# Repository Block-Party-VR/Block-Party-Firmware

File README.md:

# Block Party

Stack blocks in real life. See them stack in VR.
Play with blocks in VR. See them change in real life.
If you’re feeling brave, enter the doll house.

Virtual reality can be a powerful tool to connect the physical world and the digital world and connect people in different locations.
However, many VR experiences today are limited to the digital world.
Many multi-user VR experiences place all users into the same digital world and people in the VR headset are cut off from the physical world.

Block Party uses an asymmetric experience to connect a person using a VR headset with a person without a headset.
The person without a headset interacts with physical blocks on a physical board while the person in the VR headset interacts with digital blocks on a digital board.
When the physical user places a physical block on the physical board, the VR user sees a block in the corresponding location on the digital board.
When the physical user removes a block from the board, the corresponding digital block disappears for the VR user.
When the VR user hovers over or picks up a digital cube, the corresponding physical cube changes color to show the physical user what the VR user is doing.

## Setup
### Repository Setup
When the repository is first cloned you will need to initialize all of its submodules. 

In the terminal type: `git submodule update --init --recursive` which will initalize all of the submodules.

### Board Assemble
#### Parts List
- Foam core (scavenged)
- (4) Thor labs boxes (scavenged)
- (1) ESP32
- (1) breadboard
- copper tape
- (9) magnets
- (9) 10k resistors
board documentation can be found int he `documentation` directory.

### Cube Assembly
#### Parts List
- 3D printed case and cover (stl files are in the documentation folder)
- WS2812B LED (1 strip of 2 LEDs)
- (1) 10k resistor
- copper tape
- (2) magnets
- Kapton tape
- black electrical tape to mark the bottom
wiring diagram for the cube is in the `documentation` directory.

### Hardware Required
- Meta Quest headset. The included Unity project uses SDKs for Android so other Android-based headsets may work, but have not been tested.
- The physical board and physical blocks
- Two USB power sources to run the physical board. One for the LEDs and one for the sensors detecting where the blocks are.

### Software Dependencies
#### Unity
- [`the Singularity`](https://github.com/VRatMIT/TheSingularity-Unity)
- Meta Presence Platform: hand tracking, pokable item, interaction, hand-poke interaction, synthetic hands, grab interaction, hand-poke limiter, pass-through
- Unity package: [DOTween](https://assetstore.unity.com/packages/tools/animation/dotween-hotween-v2-27676)

#### Board
- Adafruit’s Neopixel library
- Arduino libraries

### Bluetooth Module
On v0.1 of the board, a seperate bluetooth module (HC-05) is being used for bluetooth. This module needs to be programmed when first plugged in. To program the module, disconnect it from power and hold the "EN" button on the module. (The button should be the only button on the HC-05 module). While still holding down the button, reconnect the module to the ESP32. Let go of the button and then press the ESP32's reset button. Wait 5 seconds while still holding down the "EN" button on the module, then release the button, power cycle the module, and you're done.

## Run
- Power up the board and pair it with the headset over bluetooth.
- Build and load the Unity project to the headset.
- The first time the Unity project starts on the headset, you will receive a request for Bluetooth permissions. Grant the permission and restart the app. The restart is required after permissions are granted due to current limitations on `the Singularity`.
- After restarting the app, the app should automatically connect to the physical board and respond to blocks being placed on the physical board.
- Enjoy the connection between the digital and physical world.

## Unity interactions

### Interacting with the digital blocks
Once the cube has been placed on the board a cube in VR will appear.
The VR user can poke and pickup the digital blocks which will be indicated in real life by changing the colors of the blocks. Poking will change the block color to blue and picking it up will change it to red.

### Passthrough mode
The user can activate passthrough mode inside the app to see the physical board and the digital board at the same time.

### Dollhouse mode
When the dollhouse mode is activated, the digital blocks are increased in size and the VR user is moved to the center square of the board.
Note that a physical cube on the center square of the board will not appear in the digital world.

## Board Command Docs
The board contains an ESP32 that uses bluetooth serial to send the state of the board and receive commands.

### Command Name: `BoardState`
Command Number: `0`

Format Example: `!0,X1,X2,X3,X4,X5,X6,X7,X8,X9;`

Description: This command is sent when the board state changes and describes how the board is populated.

| X1 X2 X3 |

| X4 X5 X6 |

| X7 X8 X9 |

0 corresponds with the command type. The command number for BoardState is 0.
X1 corresponds with board spot X1, and so on. The value in each of the spots indicates how many cubes are in that spot.
IE: If X1 where 3, then there would be 3 cubes in the top left spot.

If you would like to get the board state, you can send !0; to the ESP32 and it will respond with the current board state. Otherwise, the ESP32 will send the board state whenever it changes.

### Command Name `Ping`
Command Number: `1`

Format Example: `!1;`

Description: This command is sent to the ESP32 to check if it is still connected. The ESP32 will respond with `!1;` if it is still connected.

### Command Name: `SetStackColor`
Command Number: `2`

Format Example: `!2,StackNumber,Red1,Green1,Blue1,Red2,Green2,Blue2,...REDX,GREENX,BLUEX;`

Description Set the colors for one of the stacks.
- 2 corresponds with the command type. The command number for SetStackColor is 2.
- StackNumber corresponds with the stack number you want to set the colors for. See `BoardState` description for stack numbers.
- Red1, Green1, Blue1 correspond with the color of the first cube in the stack and so on. These values can be between 0-255.
You can add as many colors as you want, but they wont display if the corresponding cube doesn't physically exist.

### Command Name: `GoToIdle`
Command Number: `3`

Format Example `!3;`

Description: This command will tell the ESP32 to re-enable its idle animation. It will respond with a `!3;` when it recieves this command.

## Shout-Outs
- Thank you to all the organizers at Reality Hack and the Hardware track.
- Lucas De Bonet for creating `the Singularity` which allowed us to connect the board to Quest headsets.
- Mentor Mark Steelman for showing us the value (and complications) of runtime list creation and showing us how to make an in-editor button for debugging.
- Fellow Reality Hack hacker Sean Feeser for help with debugging.
- Juan Gil for helping us 3D print.

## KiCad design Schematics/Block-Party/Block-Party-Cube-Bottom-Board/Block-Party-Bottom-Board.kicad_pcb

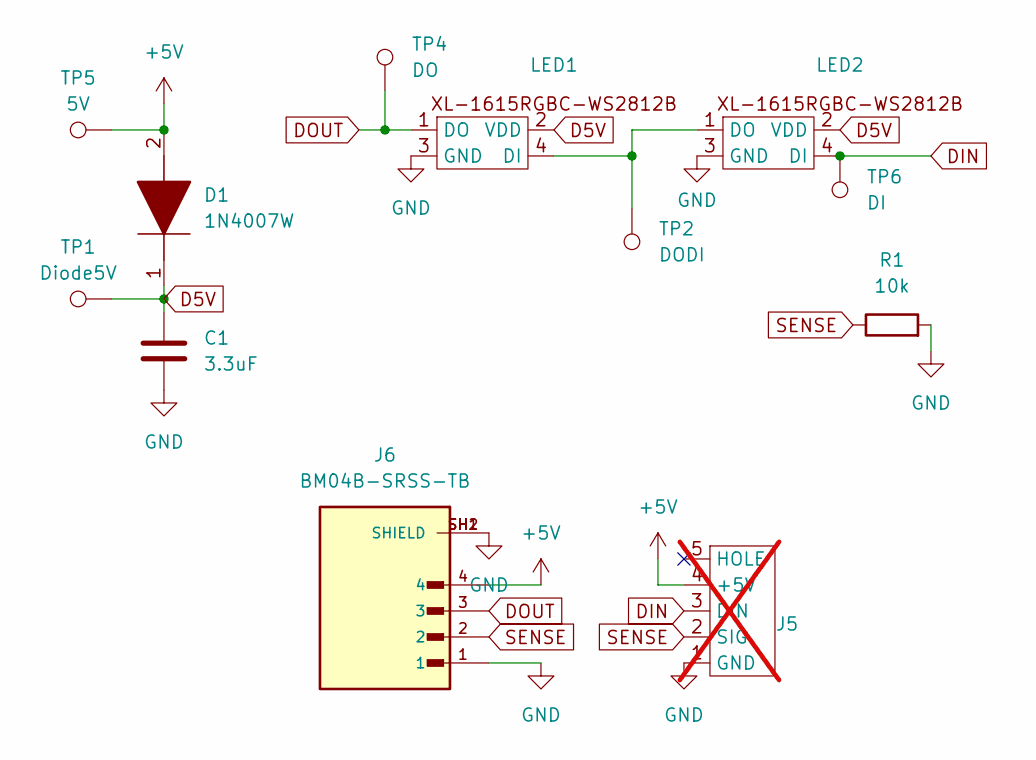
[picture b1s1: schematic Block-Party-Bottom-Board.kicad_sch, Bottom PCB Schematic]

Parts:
C1: 3.3uF; C_0805_2012Metric; Manufacturer_Part_Number CS2012X5R475K500NRE
D1: 1N4007W; Manufacturer_Part_Number 1N4007W
J5: Bottom Block Connector; not fitted
J6: BM04B-SRSS-TB; ADAFRUIT_4328; PARTREV 23/3/21
LED1: XL-1615RGBC-WS2812B; Manufacturer_Part_Number Quinn_lib:XL-1615RGBC-WS2812B
LED2: XL-1615RGBC-WS2812B; Manufacturer_Part_Number XINGLIGHT XL-1615RGBC-WS2812B
R1: 10k; R_0805_2012Metric; Manufacturer_Part_Number AC0805FR-0710KL
TP1: Diode5V; TestPoint_Pad_D1.0mm
TP2: DODI; TestPoint_Pad_D1.0mm
TP4: DO; TestPoint_Pad_D1.0mm
TP5: 5V; TestPoint_Pad_D1.0mm
TP6: DI; TestPoint_Pad_D1.0mm

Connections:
+5V: D1.2, J5.4 (+5V), J6.4, TP5.1
D5V: C1.1, D1.1, LED1.2 (VDD), LED2.2 (VDD), TP1.1
DIN: J5.3 (DIN), LED2.4 (DI), TP6.1
DOUT: J6.3, LED1.1 (DO), TP4.1
GND: C1.2, J5.1 (GND), J6.1, J6.SH1 (SHIELD), J6.SH2 (SHIELD), LED1.3 (GND), LED2.3 (GND), R1.2
unnamed: LED1.4 (DI), LED2.1 (DO), TP2.1
SENSE: J5.2 (SIG), J6.2, R1.1

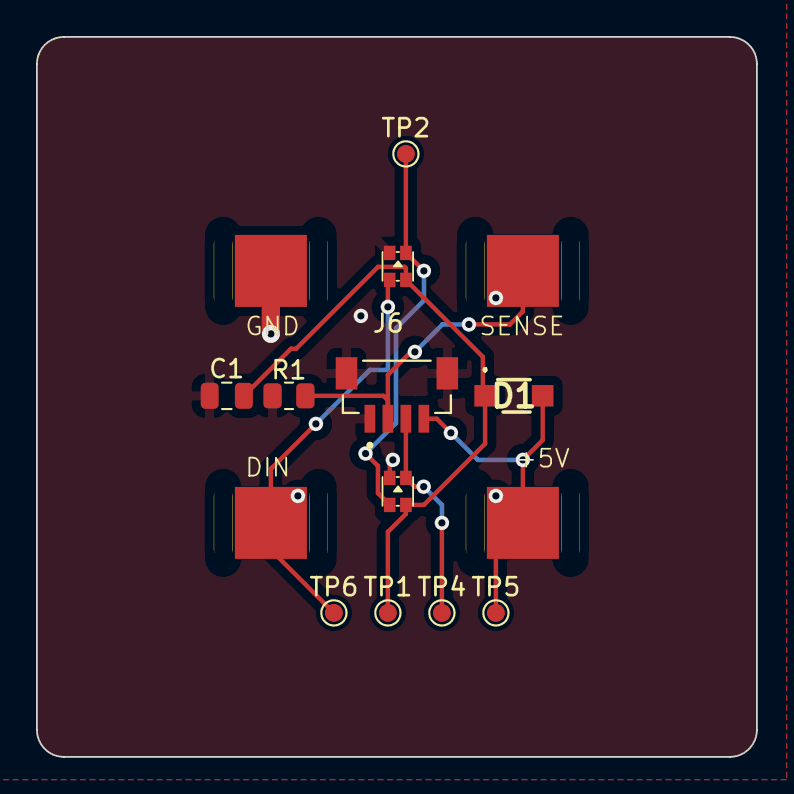
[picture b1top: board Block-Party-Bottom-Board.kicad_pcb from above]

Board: 2 copper layers, 40.0 x 40.0 mm, 12 parts (0 on the bottom side), 7 nets.

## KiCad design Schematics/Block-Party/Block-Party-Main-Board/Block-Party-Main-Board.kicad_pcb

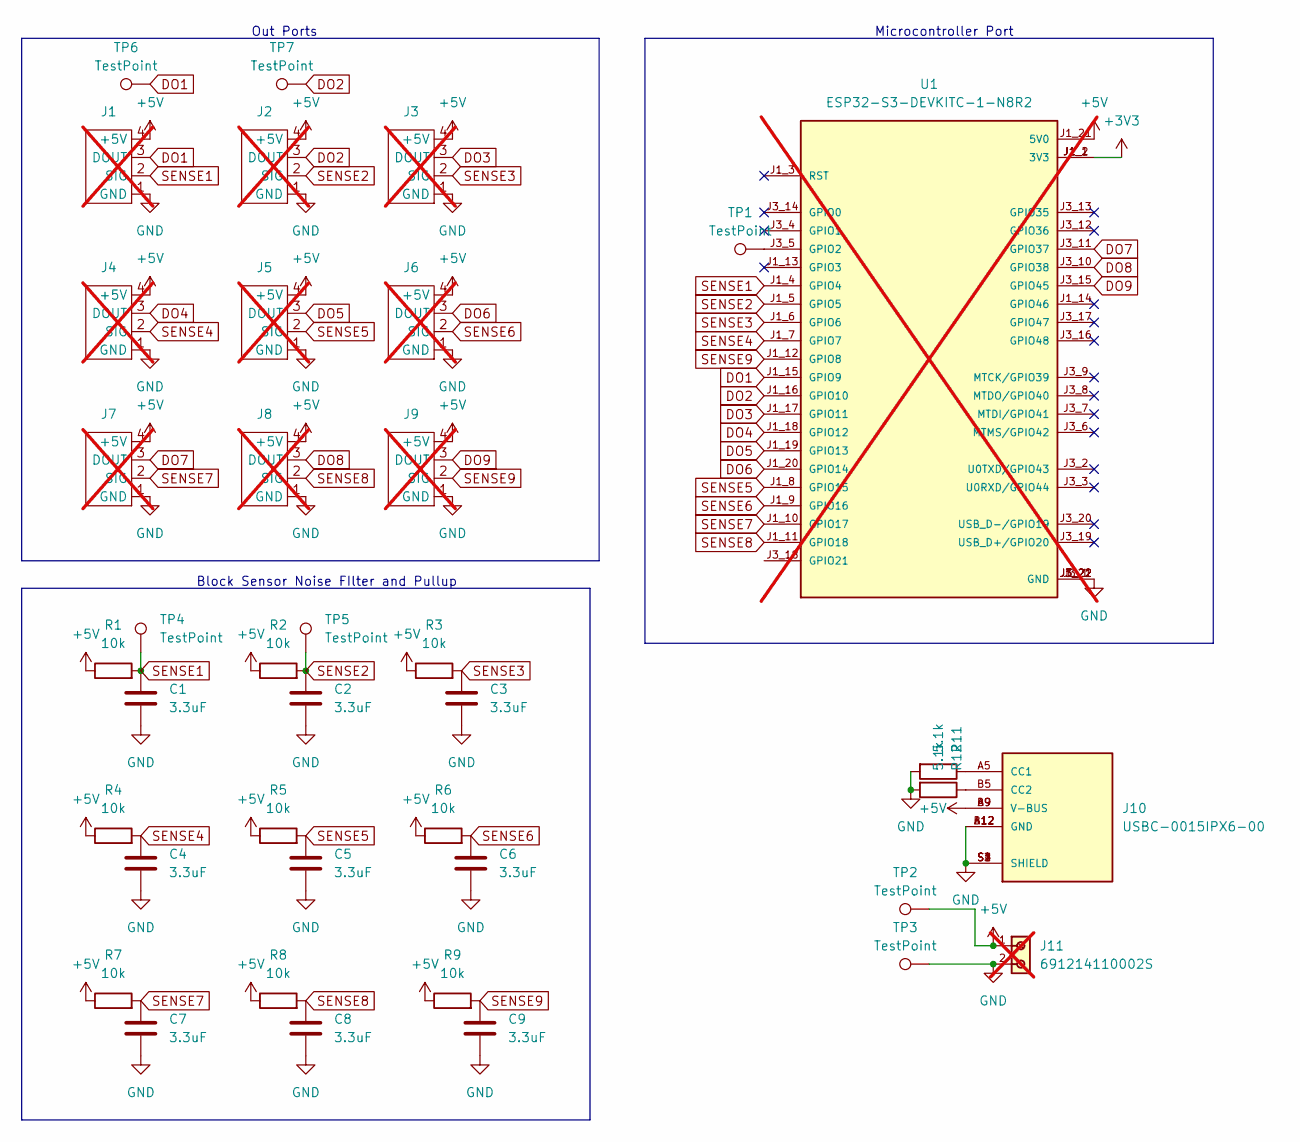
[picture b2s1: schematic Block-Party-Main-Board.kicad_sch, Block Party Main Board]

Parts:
C1, C2, C3, C4, C5, C6, C7, C8, C9: 3.3uF; C_0805_2012Metric; PART-NUMBER CS2012X5R475K500NRE
J1, J2, J3, J4, J5, J6, J7, J8, J9: Top Block Connector; not fitted
J10: USBC-0015IPX6-00; USB_C-0015IPX6-00; PARTREV 04/30/2020
J11: 691214110002S; PART-NUMBER 691214110002S; not fitted
R1, R2, R3, R4, R5, R6, R7, R8, R9: 10k; R_0805_2012Metric; PART-NUMBER AR05DTD1002
R11, R12: 5.1k; R_0805_2012Metric; PART-NUMBER CR0805-FX-5101ELF
TP1, TP2, TP3, TP4, TP5, TP6, TP7: TestPoint; TestPoint_Pad_D2.0mm
U1: ESP32-S3-DEVKITC-1-N8R2; XCVR_ESP32-S3-DEVKITC-1-N8R2; PARTREV V1; not fitted

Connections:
+3V3: U1.J1_1 (3V3), U1.J1_2 (3V3)
+5V: J1.4 (+5V), J2.4 (+5V), J3.4 (+5V), J4.4 (+5V), J5.4 (+5V), J6.4 (+5V), J7.4 (+5V), J8.4 (+5V), J9.4 (+5V), J10.A9 (V-BUS), J10.B9 (V-BUS), J11.1, R1.1, R2.1, R3.1, R4.1, R5.1, R6.1, R7.1, R8.1, R9.1, TP2.1, U1.J1_21 (5V0)
DO1: J1.3 (DOUT), TP6.1, U1.J1_15 (GPIO9)
DO2: J2.3 (DOUT), TP7.1, U1.J1_16 (GPIO10)
DO3: J3.3 (DOUT), U1.J1_17 (GPIO11)
DO4: J4.3 (DOUT), U1.J1_18 (GPIO12)
DO5: J5.3 (DOUT), U1.J1_19 (GPIO13)
DO6: J6.3 (DOUT), U1.J1_20 (GPIO14)
DO7: J7.3 (DOUT), U1.J3_11 (GPIO37)
DO8: J8.3 (DOUT), U1.J3_10 (GPIO38)
DO9: J9.3 (DOUT), U1.J3_15 (GPIO45)
GND: C1.1, C2.1, C3.1, C4.1, C5.1, C6.1, C7.1, C8.1, C9.1, J1.1 (GND), J2.1 (GND), J3.1 (GND), J4.1 (GND), J5.1 (GND), J6.1 (GND), J7.1 (GND), J8.1 (GND), J9.1 (GND), J10.A12 (GND), J10.B12 (GND), J10.S1 (SHIELD), J10.S2 (SHIELD), J10.S3 (SHIELD), J10.S4 (SHIELD), J11.2, R11.2, R12.2, TP3.1, U1.J1_22 (GND), U1.J3_1 (GND), U1.J3_21 (GND), U1.J3_22 (GND)
unnamed: J10.A5 (CC1), R11.1
unnamed: J10.B5 (CC2), R12.1
unnamed: TP1.1, U1.J3_5 (GPIO2)
SENSE1: C1.2, J1.2 (SIG), R1.2, TP4.1, U1.J1_4 (GPIO4)
SENSE2: C2.2, J2.2 (SIG), R2.2, TP5.1, U1.J1_5 (GPIO5)
SENSE3: C3.2, J3.2 (SIG), R3.2, U1.J1_6 (GPIO6)
SENSE4: C4.2, J4.2 (SIG), R4.2, U1.J1_7 (GPIO7)
SENSE5: C5.2, J5.2 (SIG), R5.2, U1.J1_8 (GPIO15)
SENSE6: C6.2, J6.2 (SIG), R6.2, U1.J1_9 (GPIO16)
SENSE7: C7.2, J7.2 (SIG), R7.2, U1.J1_10 (GPIO17)
SENSE8: C8.2, J8.2 (SIG), R8.2, U1.J1_11 (GPIO18)
SENSE9: C9.2, J9.2 (SIG), R9.2, U1.J1_12 (GPIO8)

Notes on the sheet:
Out Ports
Microcontroller Port
Block Sensor Noise FIlter and Pullup

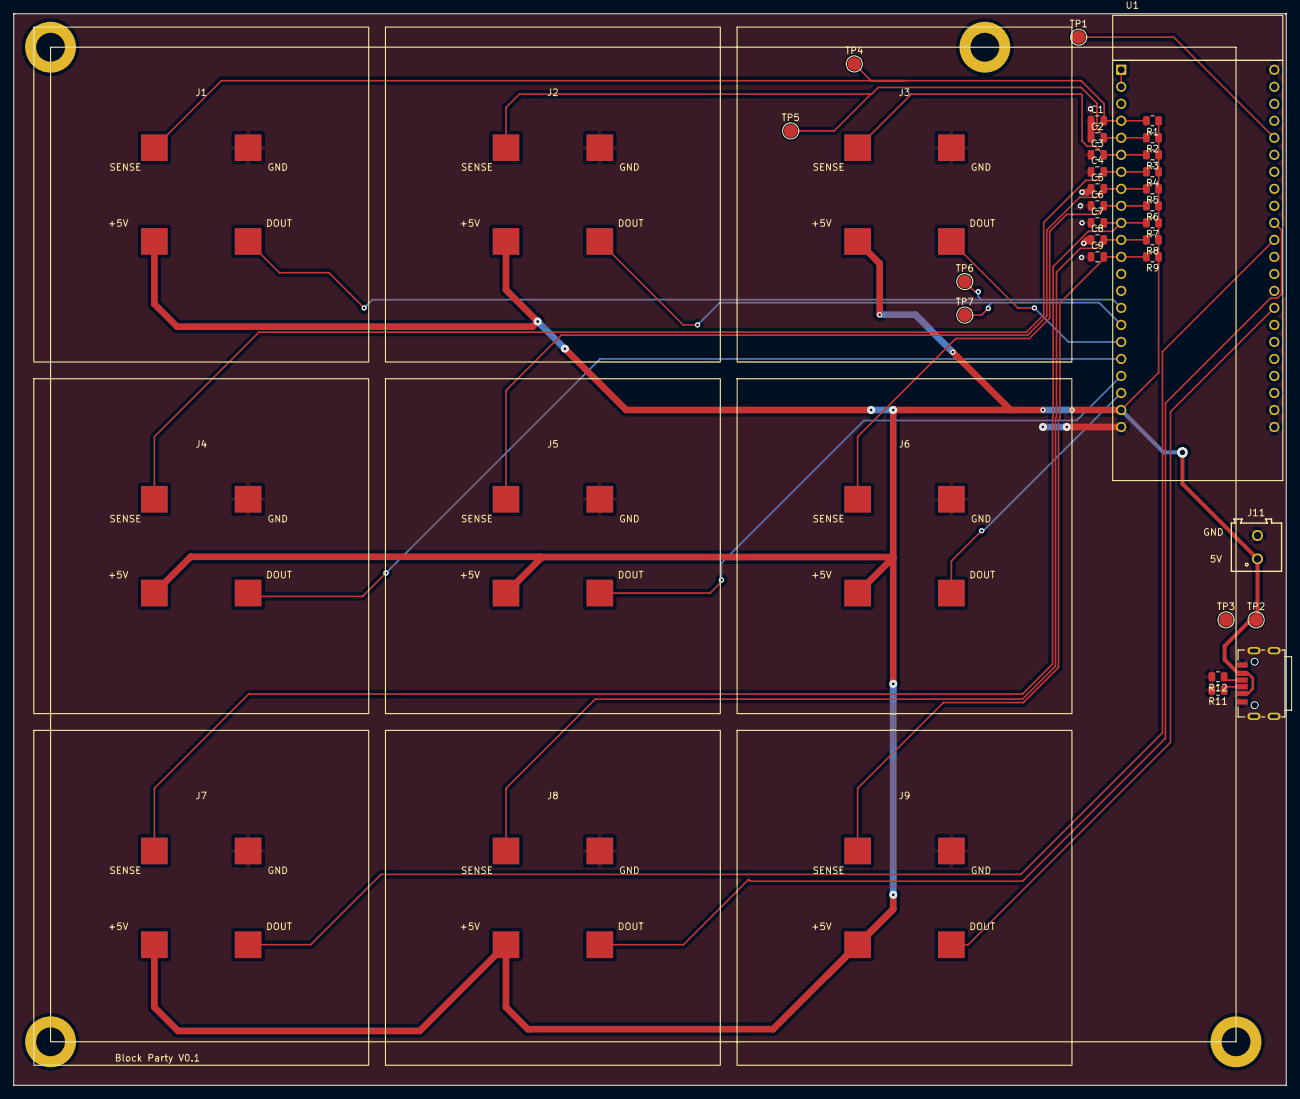
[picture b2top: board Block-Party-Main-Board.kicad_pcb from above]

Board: 2 copper layers, 190.0 x 160.0 mm, 39 parts (0 on the bottom side), 24 nets.

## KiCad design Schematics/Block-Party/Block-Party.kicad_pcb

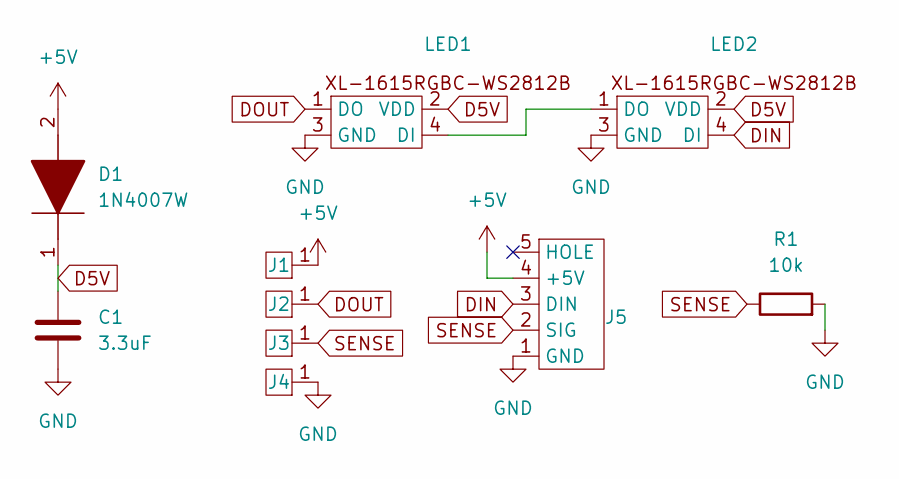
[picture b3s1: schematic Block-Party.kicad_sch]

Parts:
C1: 3.3uF; C_0805_2012Metric
D1: 1N4007W; Manufacturer_Part_Number 1N4007W
J1, J2, J3, J4: PinHeader_1x01_P2.54mm_Vertical
J5: Bottom Block Connector
LED1, LED2: XL-1615RGBC-WS2812B
R1: 10k; R_0805_2012Metric

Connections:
+5V: D1.2, J1.1, J5.4 (+5V)
D5V: C1.1, D1.1, LED1.2 (VDD), LED2.2 (VDD)
DIN: J5.3 (DIN), LED2.4 (DI)
DOUT: J2.1, LED1.1 (DO)
GND: C1.2, J4.1, J5.1 (GND), LED1.3 (GND), LED2.3 (GND), R1.2
unnamed: LED1.4 (DI), LED2.1 (DO)
SENSE: J3.1, J5.2 (SIG), R1.1

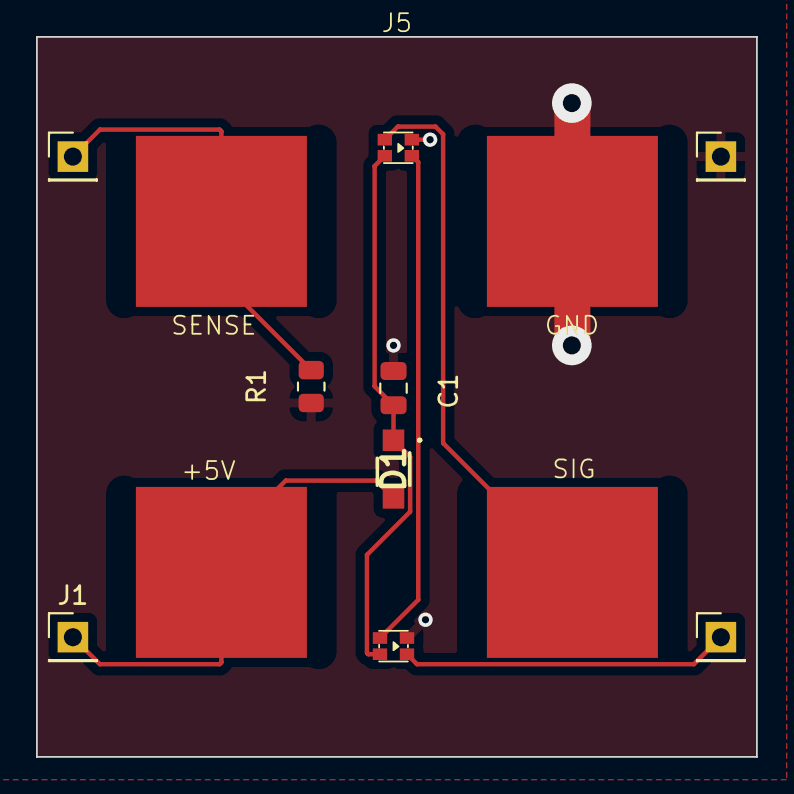
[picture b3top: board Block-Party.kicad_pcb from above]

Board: 2 copper layers, 40.0 x 40.0 mm, 10 parts (0 on the bottom side), 7 nets.

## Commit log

2024-02-10 Created bottom block schematic
2024-02-13 Created block party main board schematic
2024-02-13 Added a usb power connector.
2024-02-13 Added additional components.
2024-02-13 Finished touch up details for the bottom block board
2024-02-16 Finished v1.0 of the PCBs
2024-03-23 Misc changes.
2024-03-23 Flipped the bottom pads to be the correct orientation
2024-03-24 Added the project symbol libraries.
2024-04-20 rearranged the schematic folders
2024-04-23 Revision 1.01 of the PCBs
2024-04-23 Found a good jst part number and updated the BOMs
2024-04-29 Made the top and bottom PCB the same size
2024-05-07 Added main board mounting holes
2024-05-07 Added bottom pads to the bottom block PCB
2024-05-16 Updated micro configuration files to match the new micro we're using.
2024-06-01 Disabled serial classic and changed serial baudrate to be compatible with bluetooth classic adapter
2024-06-01 Changed baud rate to 9600 in paltformio.ini
2024-06-07 Small tweaks and an update limiter for the esp32
2024-06-10 Pulled the most up to date serial driver
2024-06-12 Added a hc05 reprogramming script
2024-06-15 Updated the bluetooth setup function and decreased the bluetooth update rate to 30fps
2024-08-12 added v0.1 to the bluetooth module name
    If you have multiple bluetooth devices paired with the same name, the quest app only connects to the first one on the list. Adding the version number lets us keep multiple versions of the board paire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
2024-08-20 Small code refactor and began using freertos tasks
2024-08-20 Added note to readme about initializing submodules
2024-08-20 Added framework for users to edit the paltformio file for machine differences without uploading the changes to github.
2024-08-22 update comment to match change in code
2024-08-22 Refactoring how board control works
2024-08-23 Completed the board manager rewrite
2024-08-23 Got the refactor building
2024-08-23 Added comments to the functions in board.h
2024-08-23 Added comments to boarddriver.h
2024-08-24 Finished commenting code changes
2024-08-25 Fixed several buffer overflow issues
2024-08-25 The board now works as expected but without idle animations
2024-08-25 Got the animator running
2024-08-25 Got the animator fades working
2024-08-25 Got the animator completed tested and working
2024-08-26 minor bug fixes and a new animation
2024-08-27 starting to build the naimation tool
2024-08-27 Set up virtual environment
2024-08-27 Organized modules into individual files
2024-08-28 Got a single frame exporting correctly
2024-08-28 You can now generate many consecutive frames
2024-08-29 added a UI class to better organize UI creation
2024-08-29 added dropdown menus
2024-08-29 Added a frame counter
2024-08-29 finished the animator tool's UI
2024-08-29 updated the animaiton tool readme
2024-09-11 removed monitor port secifiers in platformio ini
2024-09-11 updated SerialMessage submodule
2024-09-12 Re-enabled rotating animation
2024-09-12 renabled a missing animation
2024-09-24 Implimented a callback approach to processing functions
2024-09-25 Moved the lambdas to actual functions to avoid them dissapearing after setup.
2024-10-29 Fixed off by one error and updated readme
2024-11-11 Create LICENSE
